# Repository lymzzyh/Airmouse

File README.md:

# Airmouse
A air mouse with MPU-9250 and STM32F103CBT6

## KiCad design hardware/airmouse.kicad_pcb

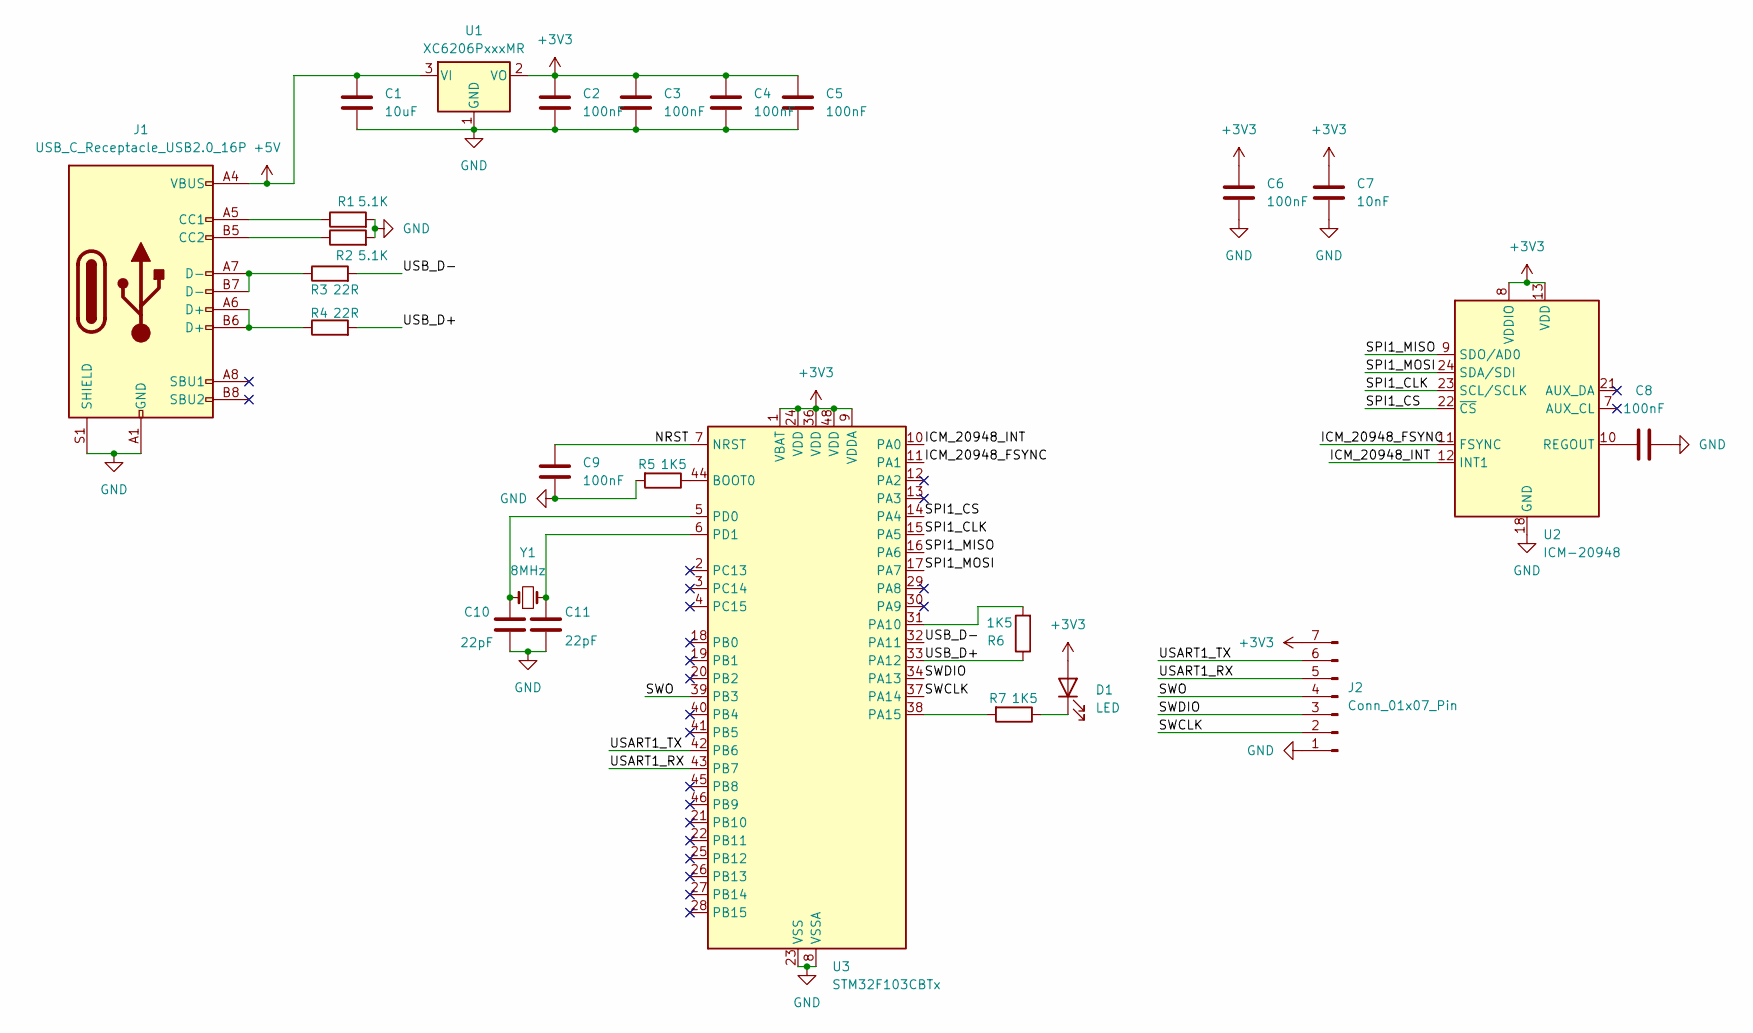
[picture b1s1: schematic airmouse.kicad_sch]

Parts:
C1: 10uF; C_0603_1608Metric
C2, C3, C4, C5, C6, C8, C9: 100nF; C_0402_1005Metric
C7: 10nF; C_0402_1005Metric
C10, C11: 22pF; C_0402_1005Metric
D1: LED; LED_0603_1608Metric
J1: USB_C_Receptacle_USB2.0_16P; USB_C_Receptacle_HRO_TYPE-C-31-M-12
J2: Conn_01x07_Pin; Hirose_DF13C_CL535-0407-6-51_1x07-1MP_P1.25mm_Vertical
R1, R2: 5.1K; R_0402_1005Metric
R3, R4: 22R; R_0402_1005Metric
R5, R6, R7: 1K5; R_0402_1005Metric
U1: XC6206PxxxMR; SOT-23-3
U2: ICM-20948; InvenSense_QFN-24_3x3mm_P0.4mm
U3: STM32F103CBTx; LQFP-48_7x7mm_P0.5mm
Y1: 8MHz; Crystal_SMD_5032-2Pin_5.0x3.2mm

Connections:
+3V3: C2.1, C3.1, C4.1, C5.1, C6.2, C7.2, D1.2 (A), J2.7, U1.2 (VO), U2.8 (VDDIO), U2.13 (VDD), U3.1 (VBAT), U3.9 (VDDA), U3.24 (VDD), U3.36 (VDD), U3.48 (VDD)
+5V: C1.1, J1.A4 (VBUS), J1.A9 (VBUS), J1.B4 (VBUS), J1.B9 (VBUS), U1.3 (VI)
/ICM_20948_FSYNC: U2.11 (FSYNC), U3.11 (PA1)
/ICM_20948_INT: U2.12 (INT1), U3.10 (PA0)
/NRST: C9.1, U3.7 (NRST)
/SPI1_CLK: U2.23 (SCL/SCLK), U3.15 (PA5)
/SPI1_CS: U2.22 (~CS), U3.14 (PA4)
/SPI1_MISO: U2.9 (SDO/AD0), U3.16 (PA6)
/SPI1_MOSI: U2.24 (SDA/SDI), U3.17 (PA7)
/SWCLK: J2.2, U3.37 (PA14)
/SWDIO: J2.3, U3.34 (PA13)
/SWO: J2.4, U3.39 (PB3)
/USART1_RX: J2.5, U3.43 (PB7)
/USART1_TX: J2.6, U3.42 (PB6)
/USB_D+: R4.2, R6.1, U3.33 (PA12)
/USB_D-: R3.2, U3.32 (PA11)
GND: C1.2, C2.2, C3.2, C4.2, C5.2, C6.1, C7.1, C8.2, C9.2, C10.2, C11.2, J1.A1 (GND), J1.A12 (GND), J1.B1 (GND), J1.B12 (GND), J1.S1 (SHIELD), J2.1, J2.MP, R1.2, R2.2, R5.2, U1.1 (GND), U2.18 (GND), U2.20 (GND), U3.8 (VSSA), U3.23 (VSS), U3.35 (VSS), U3.47 (VSS)
unnamed: D1.1 (K), R7.1
unnamed: J1.A5 (CC1), R1.1
unnamed: J1.B5 (CC2), R2.1
unnamed: J1.A6 (D+), J1.B6 (D+), R4.1
unnamed: J1.A7 (D-), J1.B7 (D-), R3.1
unnamed: C8.1, U2.10 (REGOUT)
unnamed: R5.1, U3.44 (BOOT0)
unnamed: R6.2, U3.31 (PA10)
unnamed: R7.2, U3.38 (PA15)
unnamed: C10.1, U3.5 (PD0), Y1.1
unnamed: C11.1, U3.6 (PD1), Y1.2

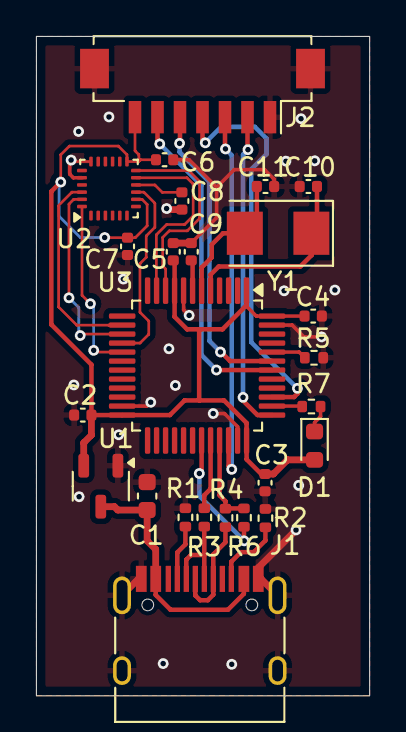
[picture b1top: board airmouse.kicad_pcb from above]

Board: 2 copper layers, 18.5 x 36.6 mm, 25 parts (0 on the bottom side), 28 nets.

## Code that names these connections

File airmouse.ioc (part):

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Mcu.Name=STM32F103C(8-B)Tx
Mcu.Package=LQFP48
Mcu.UserName=STM32F103CBTx
PA0-WKUP.GPIOParameters=GPIO_PuPd,GPIO_Label,GPIO_ModeDefaultEXTI
PA0-WKUP.GPIO_Label=ICM_INT1
PA0-WKUP.GPIO_ModeDefaultEXTI=GPIO_MODE_IT_RISING
PA0-WKUP.GPIO_PuPd=GPIO_PULLUP
PA0-WKUP.Signal=GPXTI0
PA1.GPIOParameters=GPIO_Label
PA1.GPIO_Label=ICM_FSYNC
PA1.Signal=GPIO_Output
PA10.GPIOParameters=GPIO_Label
PA10.GPIO_Label=USB_ENABLE
PA10.Signal=GPIO_Output
PA11.Mode=Device
PA11.Signal=USB_DM
PA12.Mode=Device
PA12.Signal=USB_DP
PA13.Mode=Trace_Asynchronous_SW
PA13.Signal=SYS_JTMS-SWDIO
PA14.Mode=Trace_Asynchronous_SW
PA14.Signal=SYS_JTCK-SWCLK
PA15.GPIOParameters=GPIO_Label
PA15.GPIO_Label=LED
PA15.Signal=GPIO_Output
PA4.GPIOParameters=GPIO_Label
PA4.GPIO_Label=SPI1_CS
PA4.Signal=GPIO_Output
PA5.Mode=Full_Duplex_Master
PA5.Signal=SPI1_SCK
PA6.Mode=Full_Duplex_Master
PA6.Signal=SPI1_MISO
PA7.Mode=Full_Duplex_Master
PA7.Signal=SPI1_MOSI
PB3.Mode=Trace_Asynchronous_SW
PB3.Signal=SYS_JTDO-TRACESWO
PB6.Mode=Asynchronous
PB6.Signal=USART1_TX
PB7.Mode=Asynchronous
PB7.Signal=USART1_RX
PD0-OSC_IN.Mode=HSE-External-Oscillator
PD0-OSC_IN.Signal=RCC_OSC_IN
PD1-OSC_OUT.Mode=HSE-External-Oscillator
PD1-OSC_OUT.Signal=RCC_OSC_OUT
RCC.SYSCLKFreq_VALUE=72000000
RCC.SYSCLKSource=RCC_SYSCLKSOURCE_PLLCLK
board=custom

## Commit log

2024-12-13 Add hardware
2024-12-13 修改MPU-9250为ICM-20948
2024-12-13 添加CubeMX生成的工程代码
2024-12-19 移动工程目录
2024-12-19 移除 build文件夹
2024-12-19 重新配置工程并添加LED闪烁
2024-12-19 添加Shell
2024-12-19 适配串口shell
2024-12-20 添加9轴驱动
2024-12-20 修正磁力计的读取
2024-12-20 添加低通滤波器以仅保留重力加速度分量
2025-01-08 归一化之前计算模值
